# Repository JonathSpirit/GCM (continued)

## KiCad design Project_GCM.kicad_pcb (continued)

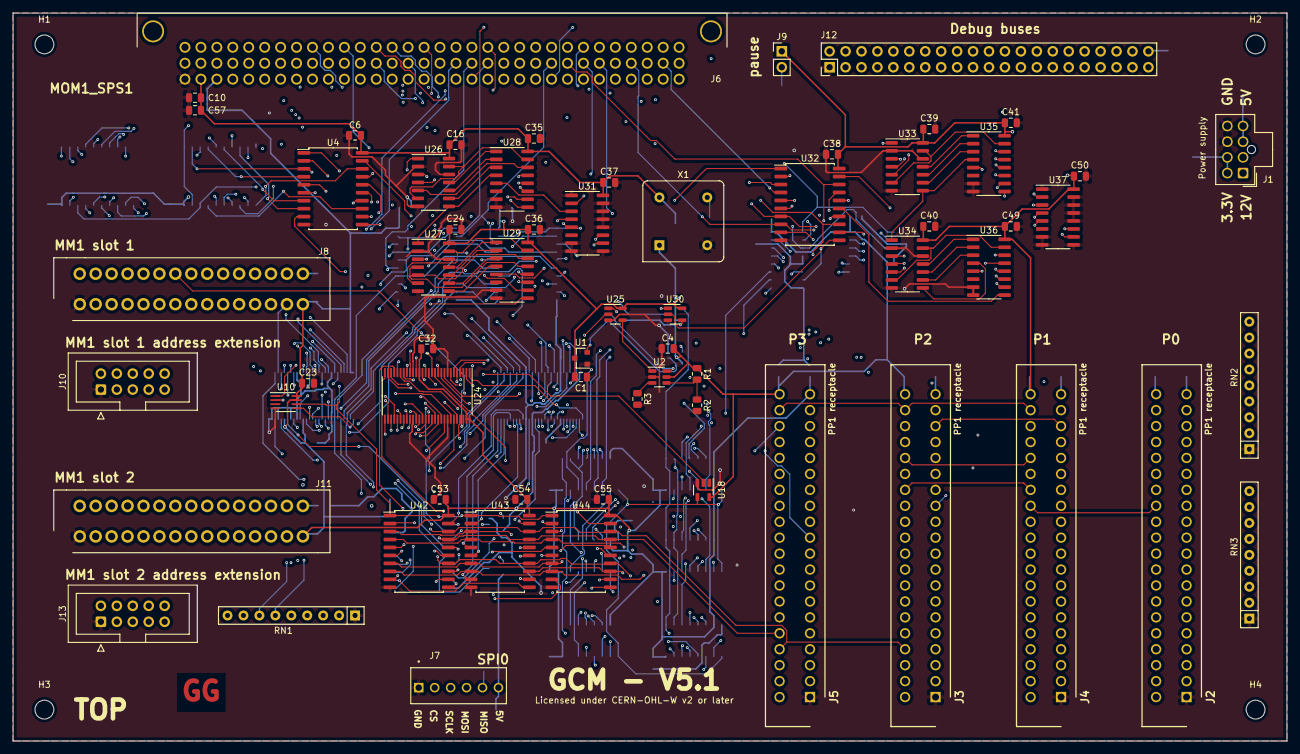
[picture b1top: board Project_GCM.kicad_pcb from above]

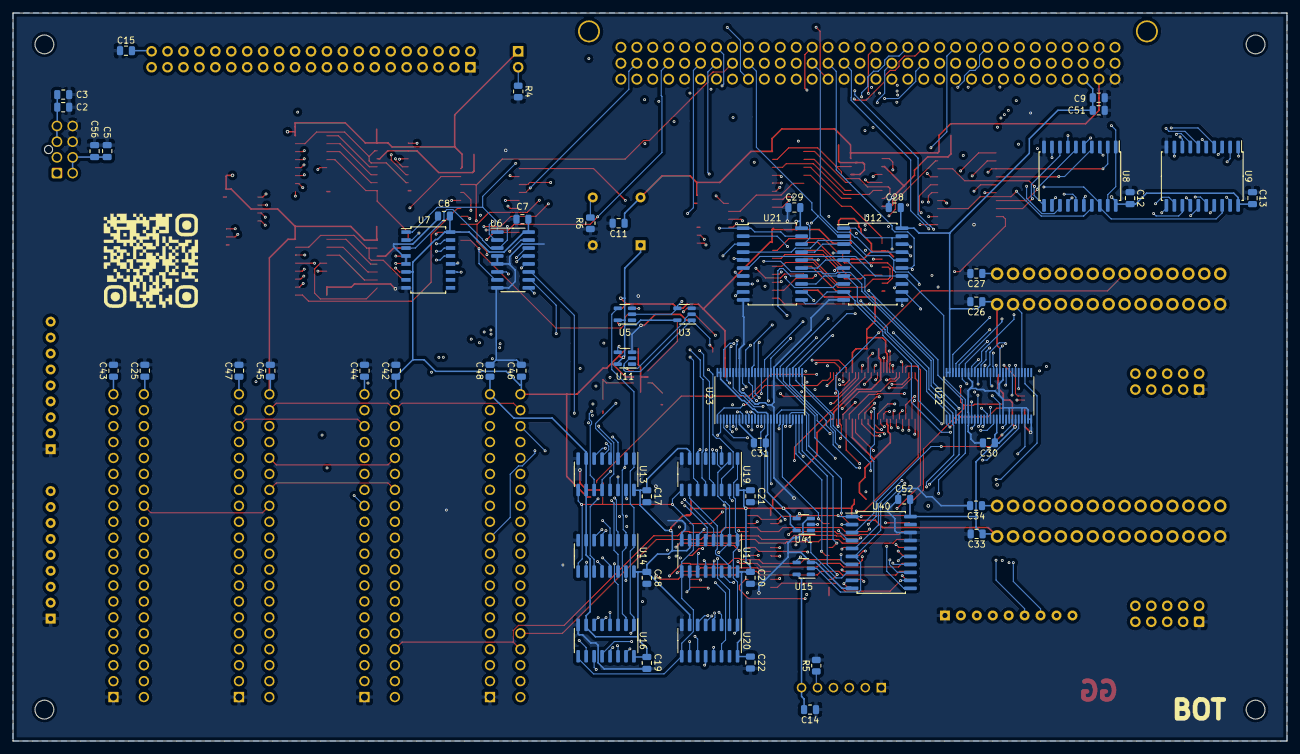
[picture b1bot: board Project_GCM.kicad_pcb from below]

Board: 4 copper layers, 203.0 x 116.0 mm, 127 parts (60 on the bottom side), 308 nets.

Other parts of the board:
C33, C34: 100nF; C_0805_2012Metric
GQR1: LOGO; QRCode
J11: MM1_receptacle_5530843-2; TE_5530843-2

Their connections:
+5V: C34.1, J11.30; also elsewhere on the board
/MEM2_~CE: J11.28; also elsewhere on the board
/MEM2_~OE: J11.27; also elsewhere on the board
/MEM2_~WE: J11.26; also elsewhere on the board
/MemoryController/MEM2DATA_0: J11.18; also elsewhere on the board
/MemoryController/MEM2DATA_1: J11.19; also elsewhere on the board
/MemoryController/MEM2DATA_2: J11.20; also elsewhere on the board
/MemoryController/MEM2DATA_3: J11.21; also elsewhere on the board
/MemoryController/MEM2DATA_4: J11.22; also elsewhere on the board
/MemoryController/MEM2DATA_5: J11.23; also elsewhere on the board
/MemoryController/MEM2DATA_6: J11.24; also elsewhere on the board
/MemoryController/MEM2DATA_7: J11.25; also elsewhere on the board
/MemorySlot2/MEMADDRESS_0: J11.2; also elsewhere on the board
/MemorySlot2/MEMADDRESS_1: J11.3; also elsewhere on the board
/MemorySlot2/MEMADDRESS_2: J11.4; also elsewhere on the board
/MemorySlot2/MEMADDRESS_3: J11.5; also elsewhere on the board
/MemorySlot2/MEMADDRESS_4: J11.6; also elsewhere on the board
/MemorySlot2/MEMADDRESS_5: J11.7; also elsewhere on the board
/MemorySlot2/MEMADDRESS_6: J11.8; also elsewhere on the board
/MemorySlot2/MEMADDRESS_7: J11.9; also elsewhere on the board
/MemorySlot2/MEMADDRESS_8: J11.10; also elsewhere on the board
/MemorySlot2/MEMADDRESS_9: J11.11; also elsewhere on the board
/MemorySlot2/MEMADDRESS_10: J11.12; also elsewhere on the board
/MemorySlot2/MEMADDRESS_11: J11.13; also elsewhere on the board
/MemorySlot2/MEMADDRESS_12: J11.14; also elsewhere on the board
/MemorySlot2/MEMADDRESS_13: J11.15; also elsewhere on the board
/MemorySlot2/MEMADDRESS_14: J11.16; also elsewhere on the board
/MemorySlot2/MEMADDRESS_15: J11.17; also elsewhere on the board
GND: C33.2, C34.2, J11.1; also elsewhere on the board

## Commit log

2020-01-09 initial upload
2020-01-30 Cleaning
2020-01-30 add diagram
2020-02-21 Create LICENSE
2020-02-21 License info on silks
2020-03-09 Adding copyright and license notice
2020-04-11 Adding schematic in PDF
2020-04-11 Adding schematics (.pdf)
2020-09-24 Changing license to "CERN-OHLw v2 or later"
2020-09-24 Applying V5.0 and license to files
2020-09-24 Creating FUNDING.yml file
2020-09-24 Creating CHANGELOG file
2020-09-24 Creating CONTRIBUTING.md file
2020-09-24 Renaming and cleaning, documents folder
2020-09-24 Renaming "librairies" folder to "libraries"
2020-09-28 Multiple change : Replacing old custom "LTC6994-1" symbol with the Kicad symbol "LTC6994xS6-1" Replacing old custom "LM810" symbol with the Kicad symbol "LM810" Replacing all hidden power pins symbol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
2020-09-29 replacing 74LVC1G74 symbol
2020-09-29 adding a potential oscillator
2020-11-15 see CHANGELOG
2020-11-16 Update materials list, begin to work on pcb
2020-11-17 First pass on the PCB
2020-11-18 Second pass on pcb
2020-11-18 Add QRcode
2020-11-23 First generation of gerbert files
2020-11-23 Removing useless doc, renaming/cleaning
2020-11-23 Removing old weird timer file and replace it with a wavedrom file
2020-11-23 Update schematics date, pdf export
2020-11-23 update PCB date, export PCB top/bot placement pdf
2020-11-27 datasheet R1, cleaning
2020-11-27 images, and blockDiagram
2020-11-27 diagram.png
2020-11-27 add datasheet in CHANGELOG
2021-02-10 Update README.md
    Set status and bugs
2021-02-15 Remove compatibility for 5.0, 4.x and add 5.1+
2021-02-15 Fix switched pins on SN74LV393A #7
2021-02-16 Removed capacitor on 12V #11
2021-02-16 Add/Modify power decoupling capacitor #10
2021-02-16 Removing ADDSCR_CLK delay #9
2021-02-16 Schematics : set version 5.1, 2021 copyright and publish date
2021-02-16 Put non-electrolytic capacitor #10
2021-02-16 Set every capacitor size to 0805
2021-02-16 Add new footprint for J7 TE_3-641124-6 #6
2021-02-16 Schematic : set pinHeader on J12 #4
2021-02-16 Netlist, apply change to board, clean track, #6 #4 #12 #10
2021-02-16 Set version to 5.1, 2021 copyright and date, replace the missing QRcode
2021-02-16 Back the MM1 connectors #8
2021-02-16 Replace capacitor for U22 U23 U24 #13
2021-02-16 Better decoupling
2021-02-16 Increase version, year to 2021, clear status
2021-02-16 Precise the molex connector for power supply
2021-02-18 First step, import ses
2021-02-24 Clean bottom layer
2021-04-12 #14 Set the BWRITE2 bus instead of BWRITE1 on U12
2021-04-14 netlist, redo autorouting and cleaning
2021-04-15 use shields.io for colored badge
2021-04-15 Update gerbert files
2021-04-15 Changelog, updated BOM
2021-04-15 Small revision on blockDiagram
2021-04-15 exporting pcb in pdf
2021-04-15 3D images, diagram.png
2021-04-15 Update schematics pdf
2021-04-15 redo wavedrom_24bitsCounter
2021-10-13 V5.1 (#15)
    * Remove compatibility for 5.0, 4.x and add 5.1+
    * Fix switched pins on SN74LV393A #7
    * Removed capacitor on 12V #11
    * Add/Modify power decoupling capacitor #10
    * Removing ADDSCR_CLK delay #9
    * Schematics : set version 5.1, 2021 copyright and publish date
